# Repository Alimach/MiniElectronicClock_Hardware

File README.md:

# MiniElectronicClock_Hardware
Проект аппаратного обеспечения мини электронных часов (ЧЭМ-1) на ATmega8 в KiCAD

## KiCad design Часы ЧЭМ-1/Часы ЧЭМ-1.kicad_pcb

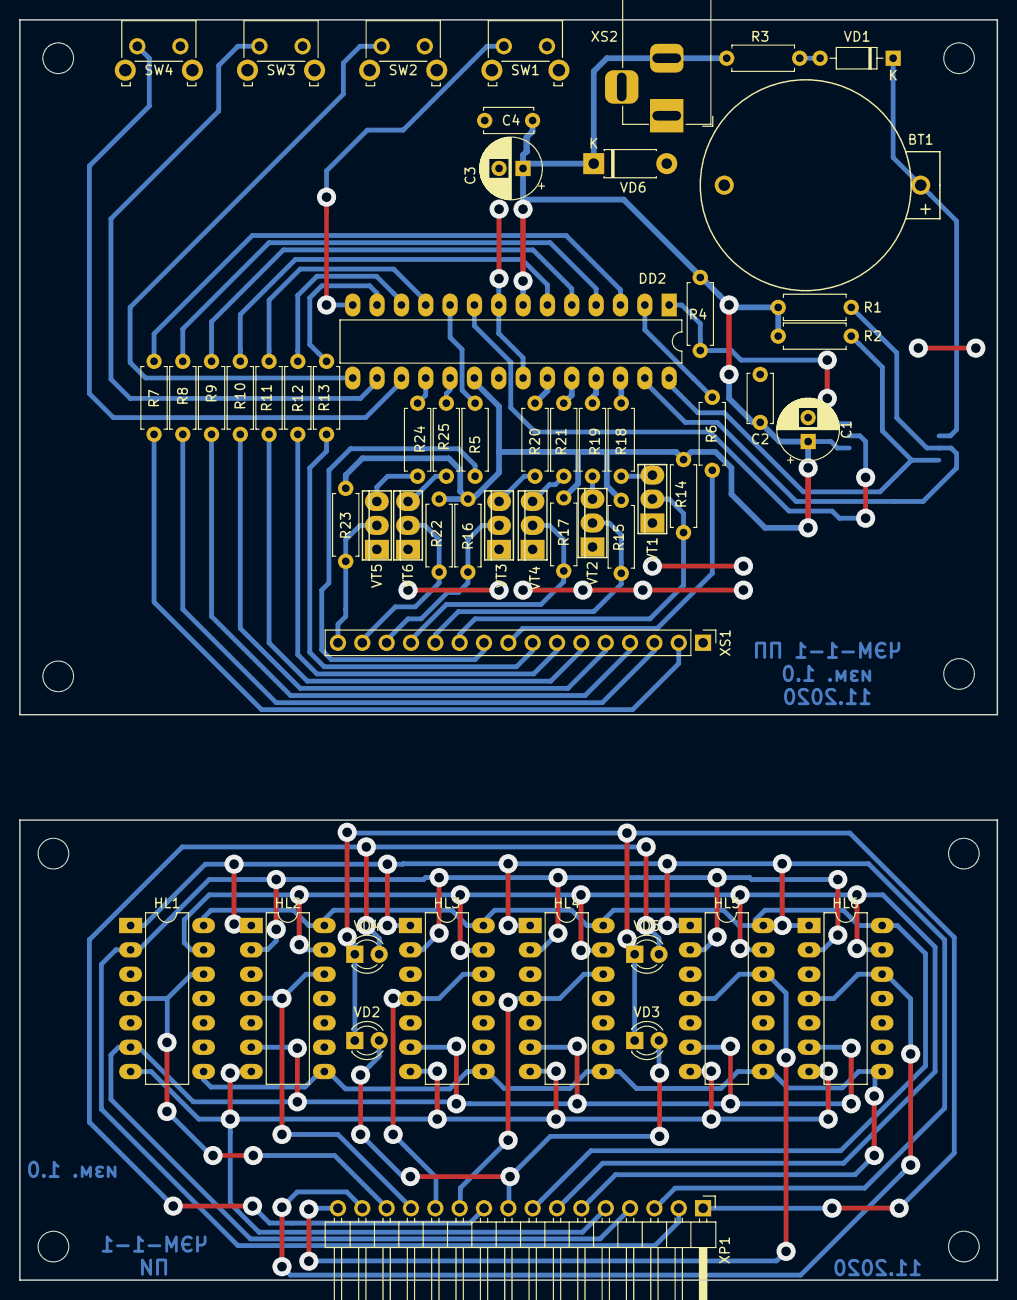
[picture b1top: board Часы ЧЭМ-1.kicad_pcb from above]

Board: 2 copper layers, 102.0 x 131.5 mm, 57 parts (1 on the bottom side), 48 nets.

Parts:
BT1: CR2032; CMA2_CR2032_ThroughHole
C1, C3: 1u; CP_Radial_D6.3mm_P2.50mm
C2, C4: 100n; C_Disc_D5.0mm_W2.5mm_P5.00mm
DD1: DS3231SN; SOIC-16W_7.5x10.3mm_Pitch1.27mm
DD2: ATmega8-16PU; DIP-28_W7.62mm_LongPads
HL1, HL2, HL3, HL4, HL5, HL6: АЛС321А1; DIP-14_W7.62mm_LongPads
R1, R2, R4, R14, R15, R16, R17, R22, R23: 10k; R_Axial_DIN0207_L6.3mm_D2.5mm_P7.62mm_Horizontal
R3: 200; R_Axial_DIN0207_L6.3mm_D2.5mm_P7.62mm_Horizontal
R5, R6, R7, R8, R9, R10, R11, R12, R13: R; R_Axial_DIN0207_L6.3mm_D2.5mm_P7.62mm_Horizontal
R18, R19, R20, R21, R24, R25: 2k; R_Axial_DIN0207_L6.3mm_D2.5mm_P7.62mm_Horizontal
SW1: +; SW_Tactile_SKHH_Angled
SW2: -; SW_Tactile_SKHH_Angled
SW3: Corr; SW_Tactile_SKHH_Angled
SW4: Mode; SW_Tactile_SKHH_Angled
VD1: 4148; D_DO-35_SOD27_P7.62mm_Horizontal
VD2, VD3, VD4, VD5: LED; LED_D3.0mm
VD6: 4007; D_DO-41_SOD81_P7.62mm_Horizontal
VT1, VT2, VT3, VT4, VT5, VT6: КТ315; КТ315(361)_Vertical
XP1: HL; Pin_Header_Angled_1x16_Pitch2.54mm
XS1: HL_In; Socket_Strip_Straight_1x16_Pitch2.54mm
XS2: Barrel_Jack_Switch; BarrelJack_Horizontal

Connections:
/A: HL1.14, HL2.14, HL3.14, HL4.14, HL5.14, HL6.14, R13.1, XP1.8, XS1.8
/B: HL1.13, HL2.13, HL3.13, HL4.13, HL5.13, HL6.13, R12.1, XP1.7, XS1.7
/C: HL1.8, HL2.8, HL3.8, HL4.8, HL5.8, HL6.8, R11.1, XP1.6, XS1.6
/D: HL1.7, HL2.7, HL3.7, HL4.7, HL5.7, HL6.7, R10.1, XP1.5, XS1.5
/DotH: R5.2, VD4.2, VD5.2, XP1.10, XS1.10
/DotL: R6.1, VD2.2, VD3.2, XP1.9, XS1.9
/E: HL1.6, HL2.6, HL3.6, HL4.6, HL5.6, HL6.6, R9.1, XP1.4, XS1.4
/F: HL1.1, HL2.1, HL3.1, HL4.1, HL5.1, HL6.1, R8.1, XP1.3, XS1.3
/G: HL1.2, HL2.2, HL3.2, HL4.2, HL5.2, HL6.2, R7.1, XP1.2, XS1.2
/K0O: HL4.4, HL4.12, R14.1, VT1.2, XP1.11, XS1.11
/K1O: HL3.4, HL3.12, R15.1, VT2.2, XP1.12, XS1.12
/K2O: HL2.4, HL2.12, R17.1, VT4.2, XP1.13, XS1.13
/K3O: HL1.4, HL1.12, R16.1, VT3.2, XP1.14, XS1.14
/K4O: HL6.4, HL6.12, R22.1, VT6.2, XP1.15, XS1.15
/K5O: HL5.4, HL5.12, R23.1, VT5.2, XP1.16, XS1.16
/K_0: DD2.26, R18.1
/K_1: DD2.25, R19.1
/K_2: DD2.24, R21.1
/K_3: DD2.23, R20.1
/K_4: DD2.19, R25.1
/K_5: DD2.18, R24.1
/Reset: DD1.4, DD2.1, R4.1
/SCL: DD1.16, DD2.28, R2.1
/SDA: DD1.15, DD2.27, R1.1
GND: BT1.2, C1.2, C2.1, C3.2, C4.1, DD1.5, DD1.6, DD1.7, DD1.8, DD1.9, DD1.10, DD1.11, DD1.12, DD1.13, DD2.8, DD2.22, SW1.2, SW2.2, SW3.2, SW4.2, VD2.1, VD3.1, VD4.1, VD5.1, VD6.2, VT1.1, VT2.1, VT3.1, VT4.1, VT5.1, VT6.1, XP1.1, XS1.1, XS2.1
unnamed: BT1.1, DD1.14, VD1.1
unnamed: DD1.3, DD2.9
unnamed: DD2.2, R6.2
unnamed: DD2.3, R7.2
unnamed: DD2.4, R8.2
unnamed: DD2.5, R9.2
unnamed: DD2.6, R10.2
unnamed: DD2.10, R5.1
unnamed: DD2.11, R11.2
unnamed: DD2.12, R12.2
unnamed: DD2.13, R13.2
unnamed: DD2.14, SW1.1
unnamed: DD2.15, SW2.1
unnamed: DD2.16, SW3.1
unnamed: DD2.17, SW4.1
unnamed: R3.1, VD1.2
unnamed: R18.2, VT1.3
unnamed: R19.2, VT2.3
unnamed: R20.2, VT3.3
unnamed: R21.2, VT4.3
unnamed: R24.2, VT5.3
unnamed: R25.2, VT6.3
VCC: C1.1, C2.2, C3.1, C4.2, DD1.2, DD2.7, DD2.20, R1.2, R2.2, R3.2, R4.2, R14.2, R15.2, R16.2, R17.2, R22.2, R23.2, VD6.1, XS2.2

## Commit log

2025-10-16 Добавление исходного старого проекта от 11.2020
2026-03-20 Спасение компонентов схемы
2026-03-20 Добавление комментариев на схему, вывод pdf
